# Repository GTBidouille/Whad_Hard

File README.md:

Bonjour, j'ai commencé à regarder la partie sniffer 40 canaux pour que cela puisse être utilisé par Whad

au début j'étais parti sur l'idée de faire 40 dongles et de les coller sur un hub usb mais je n'ai pas trouvé de hub usb assez grand, donc je serai parti sur une cascade de hub usb. Il aurait fallu gérer les tensions puis je me suis dit que peut être on pouvait faire differement

je suis parti dans l'idée de passer par un microntrolleur qui pourrait parler via SPI au module rf52840 ( en passant par la partie DMA, soit en demander au module de me prévenir quand il a des données, soit en faisant une lecture réguliere)

après mes recherches, je penche pour un STM32 ( H7,F7 ou encore H5 car ils peuvent gérer 6 bus SPI different). Cela me permettrait de limiter le nombre de CS ( en gros je lis les modules 1 de chaque carte enfant), je peux me servir du DMA pour limiter l'utilisation des modules RF, je peux buffeuriser, la vitesse est suffisante pour gerer mes 40 modules ( 5 x 8 en fait) et du coup je peux donner un résultat des 40 canaux en une seule fois.

je pense que je dois pouvoir avoir un CS commun pour les cartes sans avoir à passer par une porte NAND par exemple, il faut juste que je fasse attention au pull-up ou pull-down 

concernant la carte, j'ai choisi  la NUCLEO-F767ZI (STM32F767ZI) car elle semble convenir au besoin pour un cout plus bas que les autres. Le STM32F767ZI peut revenir à 11€ piece et la NUCLEO-F767ZI on peut la trouver à 23€

pour la partie utilisation du rf52840, je vais me baser sur le pdf schematics and PCB ainsi que sur la partie datasheet. Le cout d'un rf5280 est entre 4 et 9 €

questions: 
	- est ce que l'on part sur des antennes PCB, céramiques ou filaire
	- je pense partir sur du polling régulier mais je pourrais gérer les flux via des INT ( peut se modifier sans avoir a toucher au PCB)

je vais mettre 

broches utilisées sur le F767ZI 

pour la partie SPI ( tous en full duplex master)
| bus SPI | Miso | Mosi | CLK |
|---|---|---|---|
| SPI1 | PA6 | PA7 | PA5 | 
| SPI2 | PC2 | PC1 | PB10 | 
| SPI3 | PC11 | PB2 | PC10 | 
| SPI4 | PE5 | PE6 | PE2 | 
| SPI5 | PF8 | PF9 | PF7 | 

pour la partie CS : 
- CS1:PF13
- CS2:PF14
- CS3:PF15
- CS4:PG0
- CS5:PG1
- CS6:PE7
- CS7:PE8
- CS8:PE9

pour la partie présence
- P1:PF0
- P2:PF1
- P3:PF2
- P4:PF3
- P5:PF4

pour chaque SPI, le DMA sera activé aussi bien en TX que RX. On peut choisir le mode normal ou circular, je pense que normal est plus adapté

sur le rf52840

- p1.04 : Mosi
- p1.02 : CLK
- p1.06 : Miso
- p1.09 : /CS

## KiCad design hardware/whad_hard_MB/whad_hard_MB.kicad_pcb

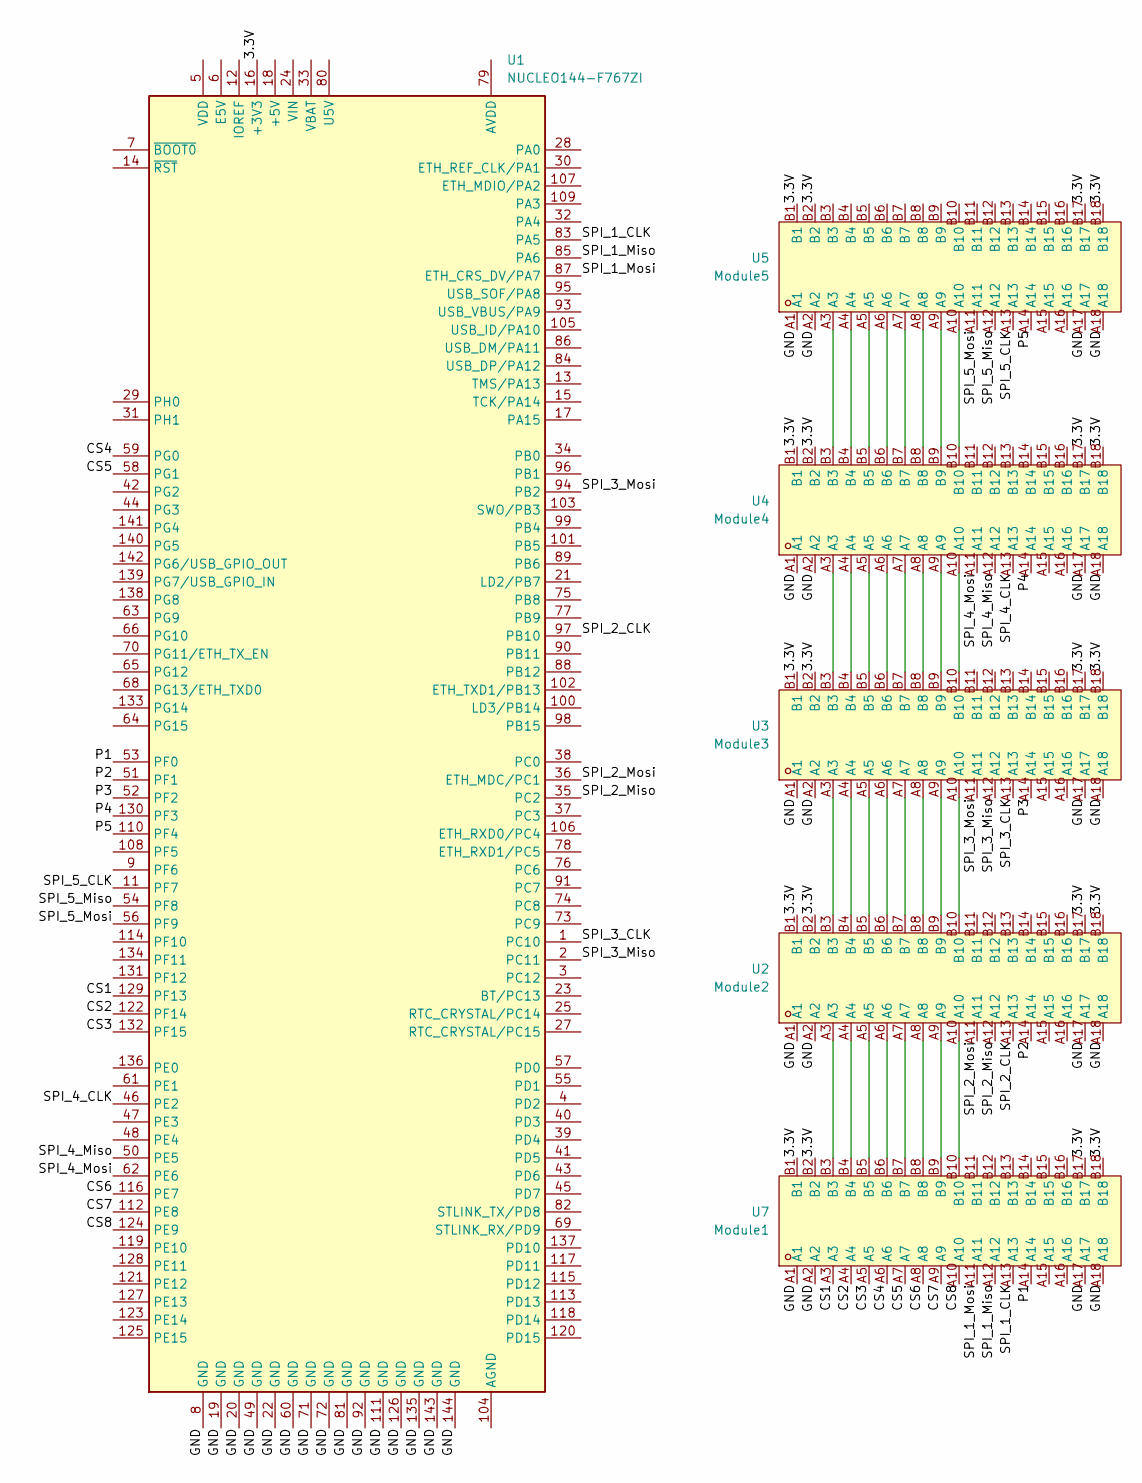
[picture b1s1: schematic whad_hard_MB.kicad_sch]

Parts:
U1: NUCLEO144-F767ZI; ST_Morpho_Connector_144_STLink
U2: Module2; CONN-TH_X3183WV-36B1-46V15; LCSC Part C5711219
U3: Module3; CONN-TH_X3183WV-36B1-46V15; LCSC Part C5711219
U4: Module4; CONN-TH_X3183WV-36B1-46V15; LCSC Part C5711219
U5: Module5; CONN-TH_X3183WV-36B1-46V15; LCSC Part C5711219
U7: Module1; CONN-TH_X3183WV-36B1-46V15; LCSC Part C5711219

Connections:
/3.3V: U1.16 (+3V3), U2.B1, U2.B2, U2.B17, U2.B18, U3.B1, U3.B2, U3.B17, U3.B18, U4.B1, U4.B2, U4.B17, U4.B18, U5.B1, U5.B2, U5.B17, U5.B18, U7.B1, U7.B2, U7.B17, U7.B18
/CS1: U1.129 (PF13), U7.A3
/CS2: U1.122 (PF14), U7.A4
/CS3: U1.132 (PF15), U7.A5
/CS4: U1.59 (PG0), U7.A6
/CS5: U1.58 (PG1), U7.A7
/CS6: U1.116 (PE7), U7.A8
/CS7: U1.112 (PE8), U7.A9
/CS8: U1.124 (PE9), U7.A10
/GND: U1.8 (GND), U1.19 (GND), U1.20 (GND), U1.22 (GND), U1.49 (GND), U1.60 (GND), U1.71 (GND), U1.72 (GND), U1.81 (GND), U1.92 (GND), U1.111 (GND), U1.126 (GND), U1.135 (GND), U1.143 (GND), U1.144 (GND), U2.A1, U2.A2, U2.A17, U2.A18, U3.A1, U3.A2, U3.A17, U3.A18, U4.A1, U4.A2, U4.A17, U4.A18, U5.A1, U5.A2, U5.A17, U5.A18, U7.A1, U7.A2, U7.A17, U7.A18
/P1: U1.53 (PF0), U7.A14
/P2: U1.51 (PF1), U2.A14
/P3: U1.52 (PF2), U3.A14
/P4: U1.130 (PF3), U4.A14
/P5: U1.110 (PF4), U5.A14
/SPI_1_CLK: U1.83 (PA5), U7.A13
/SPI_1_Miso: U1.85 (PA6), U7.A12
/SPI_1_Mosi: U1.87 (ETH_CRS_DV/PA7), U7.A11
/SPI_2_CLK: U1.97 (PB10), U2.A13
/SPI_2_Miso: U1.35 (PC2), U2.A12
/SPI_2_Mosi: U1.36 (ETH_MDC/PC1), U2.A11
/SPI_3_CLK: U1.1 (PC10), U3.A13
/SPI_3_Miso: U1.2 (PC11), U3.A12
/SPI_3_Mosi: U1.94 (PB2), U3.A11
/SPI_4_CLK: U1.46 (PE2), U4.A13
/SPI_4_Miso: U1.50 (PE5), U4.A12
/SPI_4_Mosi: U1.62 (PE6), U4.A11
/SPI_5_CLK: U1.11 (PF7), U5.A13
/SPI_5_Miso: U1.54 (PF8), U5.A12
/SPI_5_Mosi: U1.56 (PF9), U5.A11
unnamed: U2.A3, U7.B3
unnamed: U2.A4, U7.B4
unnamed: U2.A5, U7.B5
unnamed: U2.A6, U7.B6
unnamed: U2.A7, U7.B7
unnamed: U2.A8, U7.B8
unnamed: U2.A9, U7.B9
unnamed: U2.A10, U7.B10
unnamed: U2.B3, U3.A3
unnamed: U2.B4, U3.A4
unnamed: U2.B5, U3.A5
unnamed: U2.B6, U3.A6
unnamed: U2.B7, U3.A7
unnamed: U2.B8, U3.A8
unnamed: U2.B9, U3.A9
unnamed: U2.B10, U3.A10
unnamed: U3.B3, U4.A3
unnamed: U3.B4, U4.A4
unnamed: U3.B5, U4.A5
unnamed: U3.B6, U4.A6
unnamed: U3.B7, U4.A7
unnamed: U3.B8, U4.A8
unnamed: U3.B9, U4.A9
unnamed: U3.B10, U4.A10
unnamed: U4.B3, U5.A3
unnamed: U4.B4, U5.A4
unnamed: U4.B5, U5.A5
unnamed: U4.B6, U5.A6
unnamed: U4.B7, U5.A7
unnamed: U4.B8, U5.A8
unnamed: U4.B9, U5.A9
unnamed: U4.B10, U5.A10

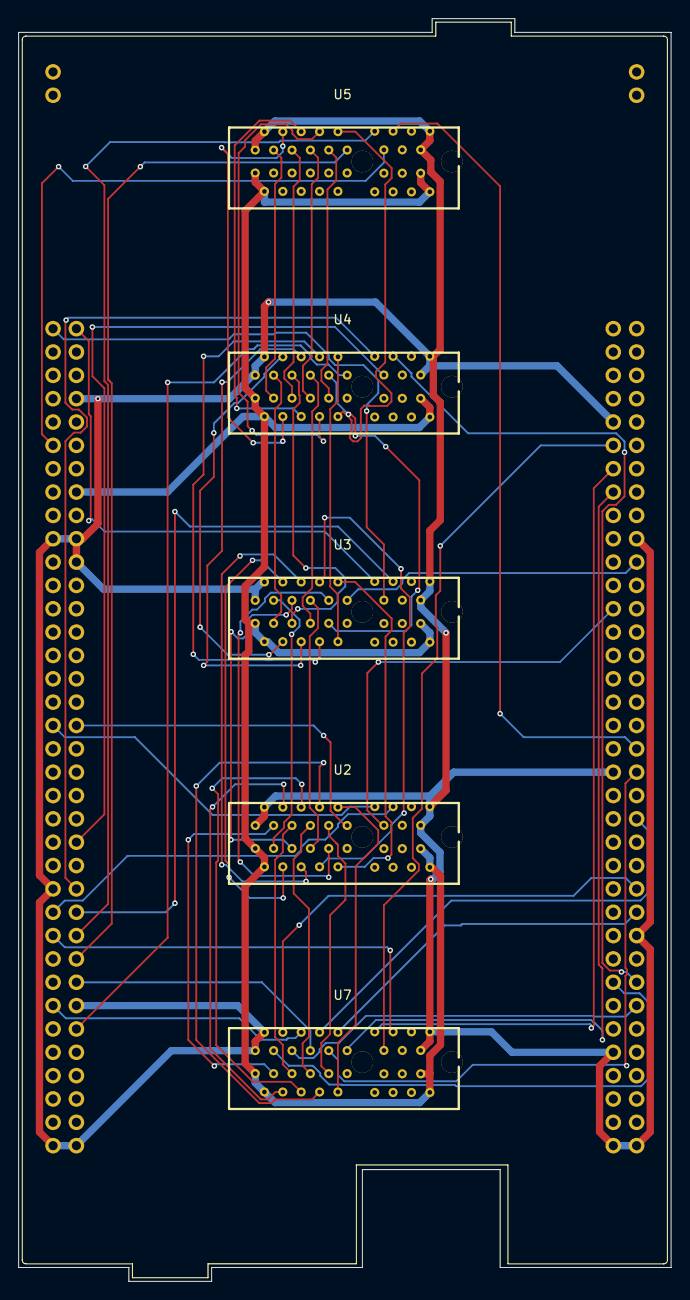
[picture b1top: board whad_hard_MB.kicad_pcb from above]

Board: 2 copper layers, 71.0 x 137.4 mm, 6 parts (0 on the bottom side), 62 nets.

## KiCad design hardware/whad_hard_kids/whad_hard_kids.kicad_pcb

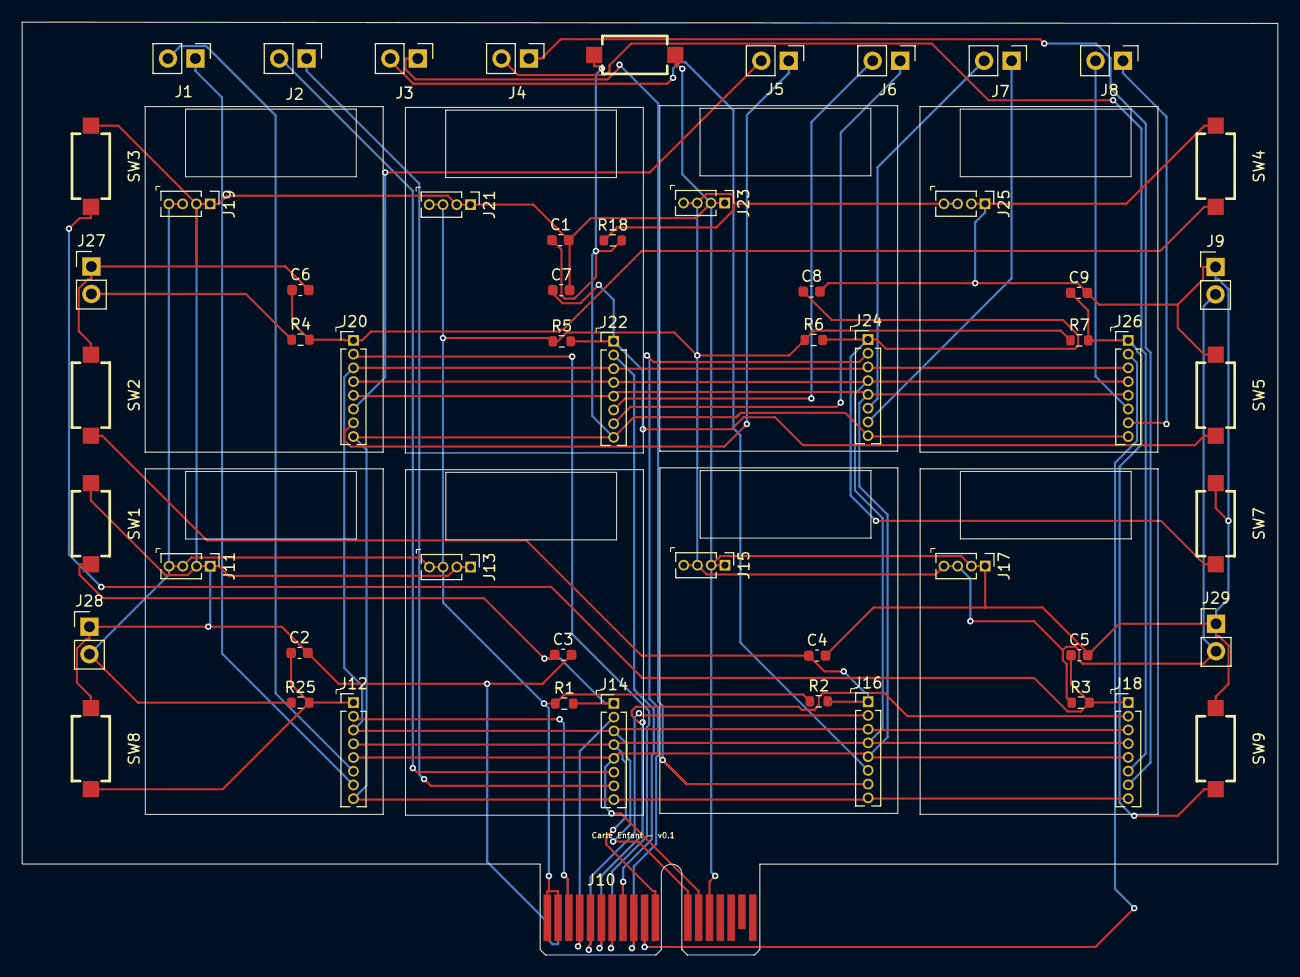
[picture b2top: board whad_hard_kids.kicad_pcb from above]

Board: 2 copper layers, 116.1 x 86.2 mm, 56 parts (0 on the bottom side), 38 nets.

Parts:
C1, C2, C3, C4, C5, C6, C7, C8, C9: 100nf; C_0603_1608Metric
J1: SWD-module1; PinHeader_1x02_P2.54mm_Vertical
J2: SWD-module2; PinHeader_1x02_P2.54mm_Vertical
J3: SWD-module3; PinHeader_1x02_P2.54mm_Vertical
J4: SWD-module14; PinHeader_1x02_P2.54mm_Vertical
J5: SWD-module5; PinHeader_1x02_P2.54mm_Vertical
J6: SWD-module6; PinHeader_1x02_P2.54mm_Vertical
J7: SWD-module7; PinHeader_1x02_P2.54mm_Vertical
J8: SWD-module8; PinHeader_1x02_P2.54mm_Vertical
J9, J27, J28, J29: SWD-Alim; PinHeader_1x02_P2.54mm_Vertical
J10: whad_Bus_PCI_Express_x1; BUS_PCIexpress_x1
J11, J13, J15, J17, J19, J21, J23, J25: Conn_01x04_Pin; PinHeader_1x04_P1.27mm_Vertical
J12, J14, J16, J18, J20, J22, J24, J26: Conn_01x08_Pin; PinHeader_1x08_P1.27mm_Vertical
R1, R2, R3, R4, R5, R6, R7, R18, R25: 10K; R_0603_1608Metric
SW1: SWI2; KEY-SMD_L6.0-W3.5-LS8.0
SW2: SWI3; KEY-SMD_L6.0-W3.5-LS8.0
SW3: SWI4; KEY-SMD_L6.0-W3.5-LS8.0
SW4: SWI5; KEY-SMD_L6.0-W3.5-LS8.0
SW5: SWI6; KEY-SMD_L6.0-W3.5-LS8.0
SW6: Reset; KEY-SMD_L6.0-W3.5-LS8.0
SW7: SWI7; KEY-SMD_L6.0-W3.5-LS8.0
SW8: SWI1; KEY-SMD_L6.0-W3.5-LS8.0
SW9: SWI8; KEY-SMD_L6.0-W3.5-LS8.0

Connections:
/3.3V: J9.2, J10.B1 (+3.3V), J10.B2 (+3.3V), J11.3, J11.4, J13.3, J13.4, J15.3, J15.4, J17.3, J17.4, J19.3, J19.4, J21.3, J21.4, J23.3, J23.4, J25.3, J25.4, J27.2, J28.2, J29.2, R1.1, R2.1, R3.1, R4.1, R5.1, R6.1, R7.1, R18.1, R25.1
/CLK: J10.B13 (SPI_CLK), J12.5, J14.5, J16.5, J18.5, J20.5, J22.5, J24.5, J26.5
/CS1: J10.A3 (CS1), J10.B3 (CS1), J12.2
/CS2: J10.A4 (CS2), J10.B4 (CS2), J14.2
/CS3: J10.A5 (CS3), J10.B5 (CS3), J16.2
/CS4: J10.A6 (CS4), J10.B6 (CS4), J18.2
/CS5: J10.A7 (CS5), J10.B7 (CS5), J20.2
/CS6: J10.A8 (CS6), J10.B8 (CS6), J22.2
/CS7: J10.A9 (CS7), J10.B9 (CS7), J24.2
/CS8: J10.A10 (CS8), J10.B10 (CS8), J26.2
/GND: C1.2, C2.2, C3.2, C4.2, C5.2, C6.2, C7.2, C8.2, C9.2, J9.1, J10.A1 (gnd), J10.A2 (gnd), J10.B14 (presence), J11.1, J11.2, J13.1, J13.2, J15.1, J15.2, J17.1, J17.2, J19.1, J19.2, J21.1, J21.2, J23.1, J23.2, J25.1, J25.2, J27.1, J28.1, J29.1, SW1.1, SW2.1, SW3.1, SW4.1, SW5.1, SW6.1, SW7.1, SW8.1, SW9.1
/Miso: J10.B12 (SPI_Miso), J12.3, J14.3, J16.3, J18.3, J20.3, J22.3, J24.3, J26.3
/Mosi: J10.B11 (SPI_Mosi), J12.4, J14.4, J16.4, J18.4, J20.4, J22.4, J24.4, J26.4
/Reset: C1.1, J12.8, J14.8, J16.8, J18.8, J20.8, J22.8, J24.8, J26.8, R18.2, SW6.2
/SWD_CLK_1: J1.1, J12.7
/SWD_CLK_2: J2.1, J14.7
/SWD_CLK_3: J3.1, J16.7
/SWD_CLK_4: J4.1, J18.7
/SWD_CLK_5: J5.1, J20.7
/SWD_CLK_6: J6.1, J22.7
/SWD_CLK_7: J7.1, J24.7
/SWD_CLK_8: J8.1, J26.7
/SWD_IO_1: J1.2, J12.6
/SWD_IO_2: J2.2, J14.6
/SWD_IO_3: J3.2, J16.6
/SWD_IO_4: J4.2, J18.6
/SWD_IO_5: J5.2, J20.6
/SWD_IO_6: J6.2, J22.6
/SWD_IO_7: J7.2, J24.6
/SWD_IO_8: J8.2, J26.6
/SWI1: C2.1, J12.1, R25.2, SW8.2
/SWI2: C3.1, J14.1, R1.2, SW1.2
/SWI3: C4.1, J16.1, R2.2, SW2.2
/SWI4: C5.1, J18.1, R3.2, SW3.2
/SWI5: C6.1, J20.1, R4.2, SW4.2
/SWI6: C7.1, J22.1, R5.2, SW5.2
/SWI7: C8.1, J24.1, R6.2, SW7.2
/SWI8: C9.1, J26.1, R7.2, SW9.2

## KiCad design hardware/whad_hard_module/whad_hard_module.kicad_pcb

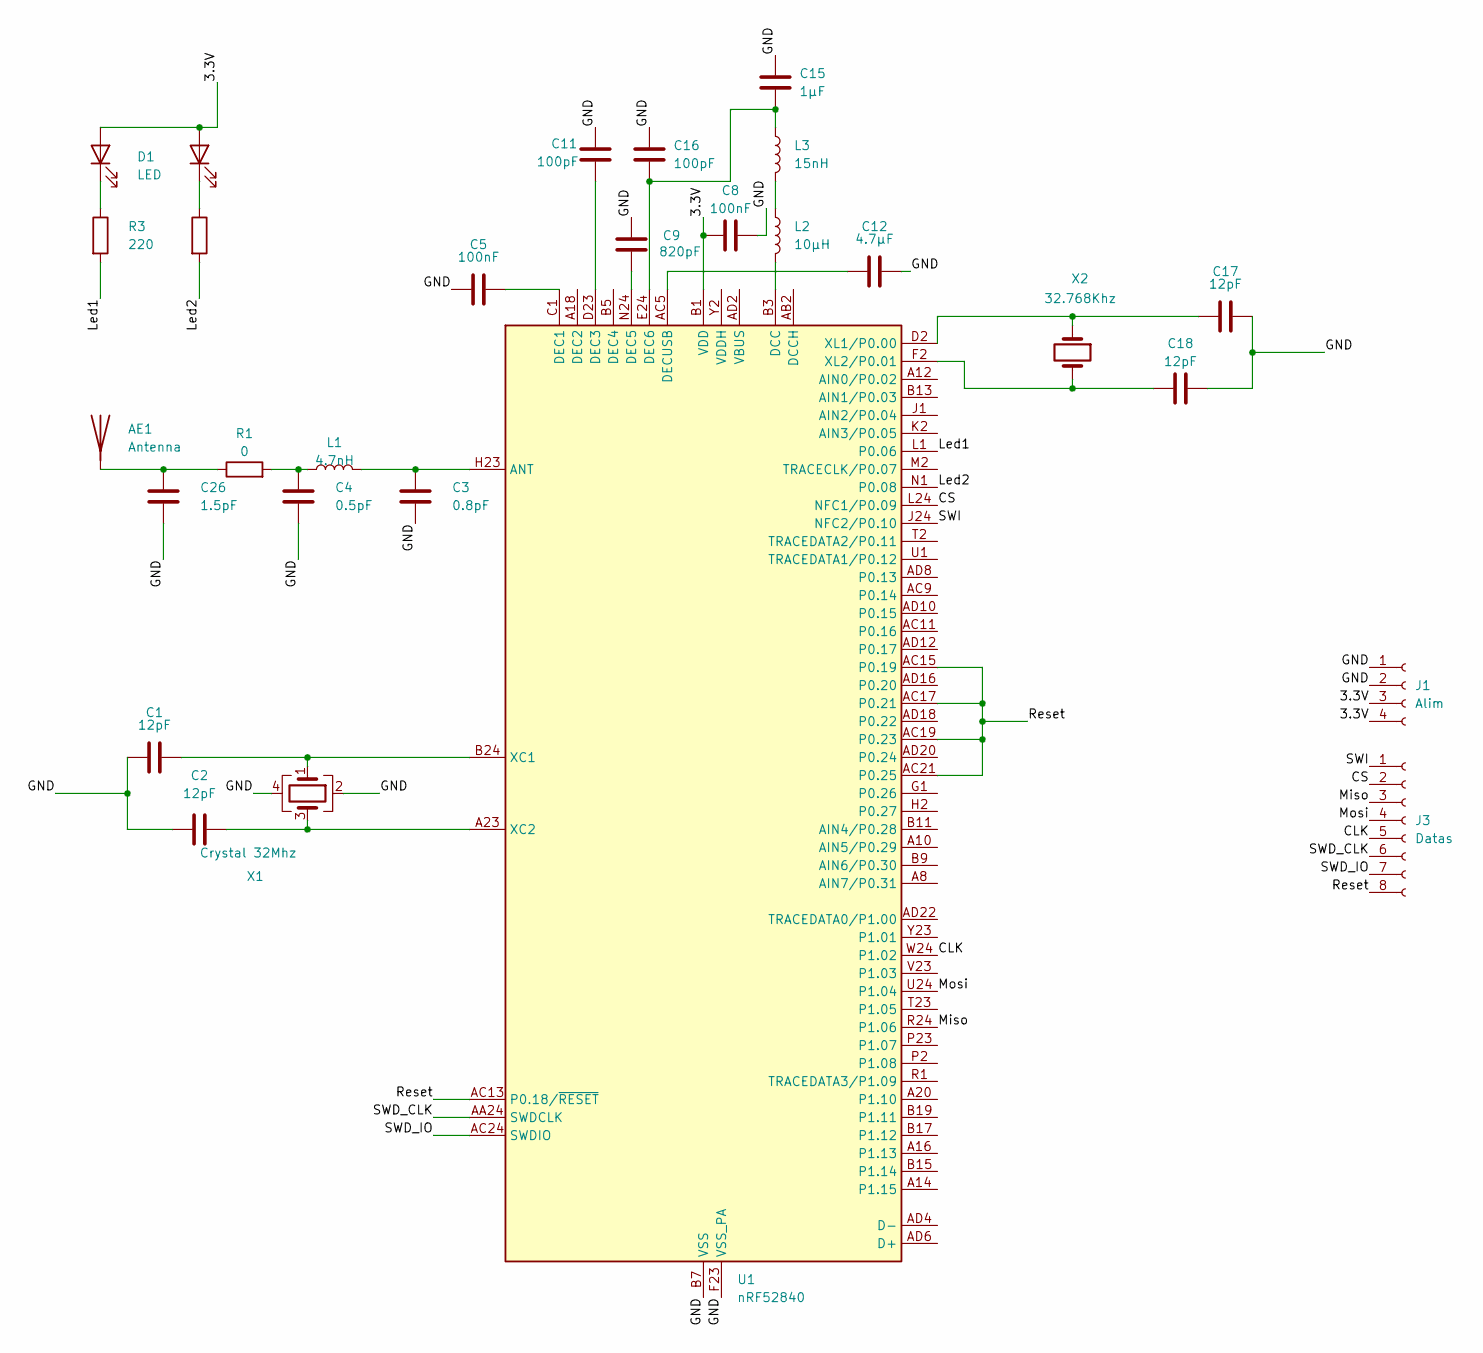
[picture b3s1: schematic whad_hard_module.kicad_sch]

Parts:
AE1: Antenna; antenne_2_4G
C1, C2, C17, C18: 12pF; C_0603_1608Metric
C3: 0.8pF; C_0603_1608Metric
C4: 0.5pF; C_0603_1608Metric
C5, C8: 100nF; C_0603_1608Metric
C9: 820pF; C_0603_1608Metric
C11, C16: 100pF; C_0603_1608Metric
C12: 4.7µF; C_0603_1608Metric
C15: 1µF; C_0603_1608Metric
C26: 1.5pF; C_0603_1608Metric
D1, D2: LED; LED_0603_1608Metric
J1: Alim; PinHeader_1x04_P1.27mm_Vertical
J3: Datas; PinHeader_1x08_P1.27mm_Vertical
L1: 4.7nH; L_0603_1608Metric
L2: 10µH; L_0603_1608Metric
L3: 15nH; L_0402_1005Metric
R1: 0; R_0603_1608Metric
R3, R4: 220; R_0603_1608Metric
U1: nRF52840; Nordic_AQFN-73-1EP_7x7mm_P0.5mm
X1: Crystal 32Mhz; Crystal_SMD_2016-4Pin_2.0x1.6mm
X2: 32.768Khz; Crystal_SMD_2012-2Pin_2.0x1.2mm

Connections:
/3.3V: C8.2, D1.2 (A), D2.2 (A), J1.3, J1.4, U1.A22 (VDD), U1.AD14 (VDD), U1.AD23 (VDD), U1.B1 (VDD), U1.W1 (VDD)
/CLK: J3.5, U1.W24 (P1.02)
/CS: J3.2, U1.L24 (NFC1/P0.09)
/GND: C1.2, C2.2, C3.1, C4.1, C5.2, C8.1, C9.2, C11.2, C12.2, C15.2, C16.2, C17.2, C18.2, C26.1, J1.1, J1.2, U1.B7 (VSS), U1.EP (VSS), U1.F23 (VSS_PA), X1.2, X1.4
/Led1: R3.2, U1.L1 (P0.06)
/Led2: R4.2, U1.N1 (P0.08)
/Miso: J3.3, U1.R24 (P1.06)
/Mosi: J3.4, U1.U24 (P1.04)
/Reset: J3.8, U1.AC13 (P0.18/~RESET), U1.AC15 (P0.19), U1.AC17 (P0.21), U1.AC19 (P0.23), U1.AC21 (P0.25)
/SWD_CLK: J3.6, U1.AA24 (SWDCLK)
/SWD_IO: J3.7, U1.AC24 (SWDIO)
/SWI: J3.1, U1.J24 (NFC2/P0.10)
unnamed: AE1.1 (A), C26.2, R1.1
unnamed: C4.2, L1.1, R1.2
unnamed: D1.1 (K), R3.1
unnamed: D2.1 (K), R4.1
unnamed: L2.1, L3.2
unnamed: C3.2, L1.2, U1.H23 (ANT)
unnamed: L2.2, U1.B3 (DCC)
unnamed: C5.1, U1.C1 (DEC1)
unnamed: C11.1, U1.D23 (DEC3)
unnamed: C9.1, U1.N24 (DEC5)
unnamed: C15.1, C16.1, L3.1, U1.E24 (DEC6)
unnamed: C12.1, U1.AC5 (DECUSB)
unnamed: C1.1, U1.B24 (XC1), X1.1
unnamed: C2.1, U1.A23 (XC2), X1.3
unnamed: C17.1, U1.D2 (XL1/P0.00), X2.1
unnamed: C18.1, U1.F2 (XL2/P0.01), X2.2

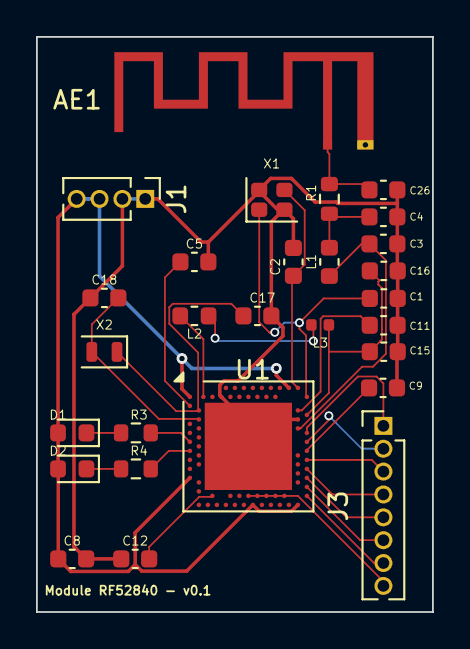
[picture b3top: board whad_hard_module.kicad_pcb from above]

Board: 2 copper layers, 22.0 x 31.9 mm, 28 parts (0 on the bottom side), 28 nets.

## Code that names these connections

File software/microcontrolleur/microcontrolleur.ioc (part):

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Mcu.Name=STM32F767ZITx
Mcu.Package=LQFP144
Mcu.UserName=STM32F767ZITx
PA5.Mode=Full_Duplex_Master
PA5.Signal=SPI1_SCK
PA6.Mode=Full_Duplex_Master
PA6.Signal=SPI1_MISO
PA7.Mode=Full_Duplex_Master
PA7.Signal=SPI1_MOSI
PB10.Mode=Full_Duplex_Master
PB10.Signal=SPI2_SCK
PB2.Mode=Full_Duplex_Master
PB2.Signal=SPI3_MOSI
PC1.Mode=Full_Duplex_Master
PC1.Signal=SPI2_MOSI
PC10.Mode=Full_Duplex_Master
PC10.Signal=SPI3_SCK
PC11.Mode=Full_Duplex_Master
PC11.Signal=SPI3_MISO
PC2.Mode=Full_Duplex_Master
PC2.Signal=SPI2_MISO
PE2.Mode=Full_Duplex_Master
PE2.Signal=SPI4_SCK
PE5.Mode=Full_Duplex_Master
PE5.Signal=SPI4_MISO
PE6.Mode=Full_Duplex_Master
PE6.Signal=SPI4_MOSI
PE7.GPIOParameters=GPIO_Label
PE7.GPIO_Label=CS6
PE7.Signal=GPIO_Output
PE8.GPIOParameters=GPIO_Label
PE8.GPIO_Label=CS7
PE8.Signal=GPIO_Output
PE9.GPIOParameters=GPIO_Label
PE9.GPIO_Label=CS8
PE9.Signal=GPIO_Output
PF13.GPIOParameters=GPIO_Label
PF13.GPIO_Label=CS1
PF13.Signal=GPIO_Output
PF14.GPIOParameters=GPIO_Label
PF14.GPIO_Label=CS2
PF14.Signal=GPIO_Output
PF15.GPIOParameters=GPIO_Label
PF15.GPIO_Label=CS3
PF15.Signal=GPIO_Output
PF7.Mode=Full_Duplex_Master
PF7.Signal=SPI5_SCK
PF8.Mode=Full_Duplex_Master
PF8.Signal=SPI5_MISO
PF9.Mode=Full_Duplex_Master
PF9.Signal=SPI5_MOSI
PG0.GPIOParameters=GPIO_Label
PG0.GPIO_Label=CS4
PG0.Signal=GPIO_Output
PG1.GPIOParameters=GPIO_Label
PG1.GPIO_Label=CS5
PG1.Signal=GPIO_Output
RCC.HSE_VALUE=25000000
board=custom

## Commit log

2025-10-06 premier commit
2025-10-06 maj README
